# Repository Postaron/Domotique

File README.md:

#Domotique

Projet en cours pour contrôler la température/radiateur et la lumière/luminosité par le biais du RFID 
(tag) et d'un petit écran LCD, le tout par le bus I²C

#Projet non fini

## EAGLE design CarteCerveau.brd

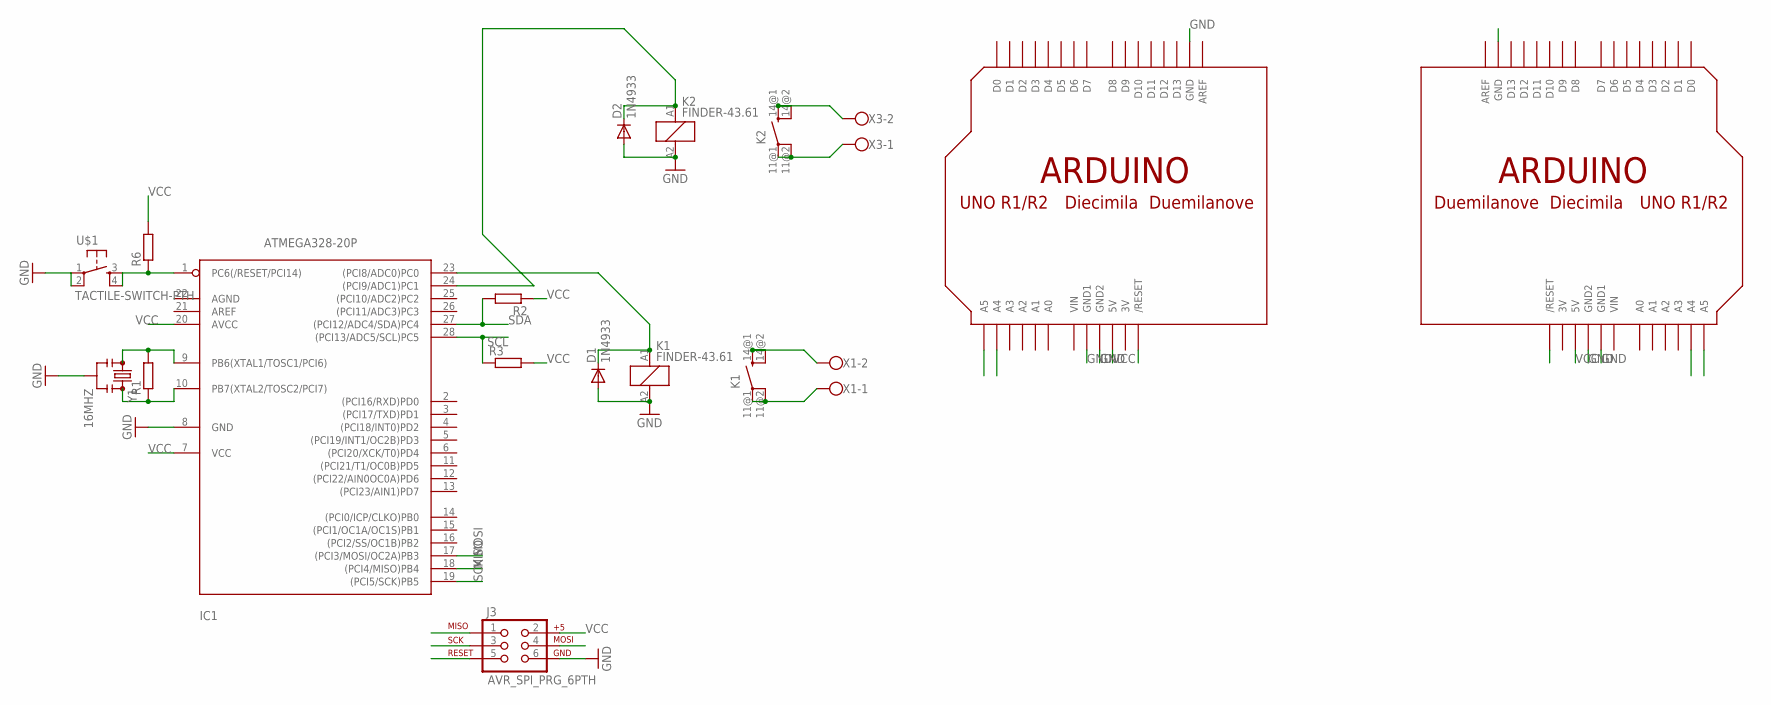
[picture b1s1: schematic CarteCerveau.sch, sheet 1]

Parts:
D1, D2: 1N4933; DO41-10
IC1: ATMEGA328-20P; DIL28-3
J3: AVR_SPI_PRG_6PTH; 2X3
K1, K2: FINDER-43.61
R1, R2, R3, R6: R-EU_R1206; R1206
U$1: TACTILE-SWITCH-PTH; TAC-SWITCH-PTH
U$2, U$3: ARDUINO-NOHOLE
X1, X3: W237-102
Y1: 16MHZ; RESONATOR-SMD

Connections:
3V: U$2.3V, U$3.3V
GND: D1.A, D2.A, IC1.8 (GND), J3.6, K1.A2 (2), K2.A2 (2), U$1.1, U$1.2, U$2.GND, U$2.GND1, U$2.GND2, U$3.GND, U$3.GND1, U$3.GND2, Y1.2; also elsewhere on the board
MISO: IC1.18 ((PCI4/MISO)PB4), J3.1
MOSI: IC1.17 ((PCI3/MOSI/OC2A)PB3), J3.4
unnamed: IC1.9 (PB6(XTAL1/TOSC1/PCI6)), R1.2, Y1.1
unnamed: IC1.10 (PB7(XTAL2/TOSC2/PCI7)), R1.1, Y1.3
unnamed: D1.C, IC1.23 ((PCI8/ADC0)PC0), K1.A1 (1)
unnamed: K1.14@1 (SA), K1.14@2 (SB), X1.2
unnamed: K1.11@1 (PA), K1.11@2 (PB), X1.1
unnamed: D2.C, IC1.24 ((PCI9/ADC1)PC1), K2.A1 (1)
unnamed: K2.14@1 (SA), K2.14@2 (SB), X3.2
unnamed: K2.11@1 (PA), K2.11@2 (PB), X3.1
RST: IC1.1 (PC6(/RESET/PCI14)), J3.5, R6.1, U$1.3, U$1.4, U$2.RESET (/RESET), U$3.RESET (/RESET)
SCK: IC1.19 ((PCI5/SCK)PB5), J3.3
SCL: IC1.28 ((PCI13/ADC5/SCL)PC5), R3.1, U$2.A5, U$3.A5
SDA: IC1.27 ((PCI12/ADC4/SDA)PC4), R2.2, U$2.A4, U$3.A4
VCC: IC1.7 (VCC), IC1.20 (AVCC), J3.2, R2.1, R3.2, R6.2, U$2.5V, U$3.5V; also elsewhere on the board
VIN: U$2.VIN, U$3.VIN

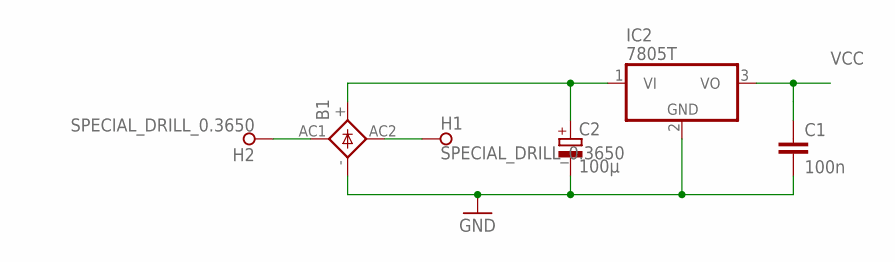
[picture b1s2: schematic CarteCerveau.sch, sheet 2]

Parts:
B1: 2KBB-R
C1: 100n; C1206
C2: 100µ; B45181A
H1, H2: SPECIAL_DRILL_0.3650; PAD_0.3650
IC2: 7805T; TO220H

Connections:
GND: B1.-, C1.2, C2.-, IC2.2 (GND); also elsewhere on the board
unnamed: B1.AC1, H2.1
unnamed: B1.AC2, H1.1
unnamed: B1.+, C2.+, IC2.1 (VI)
VCC: C1.1, IC2.3 (VO); also elsewhere on the board

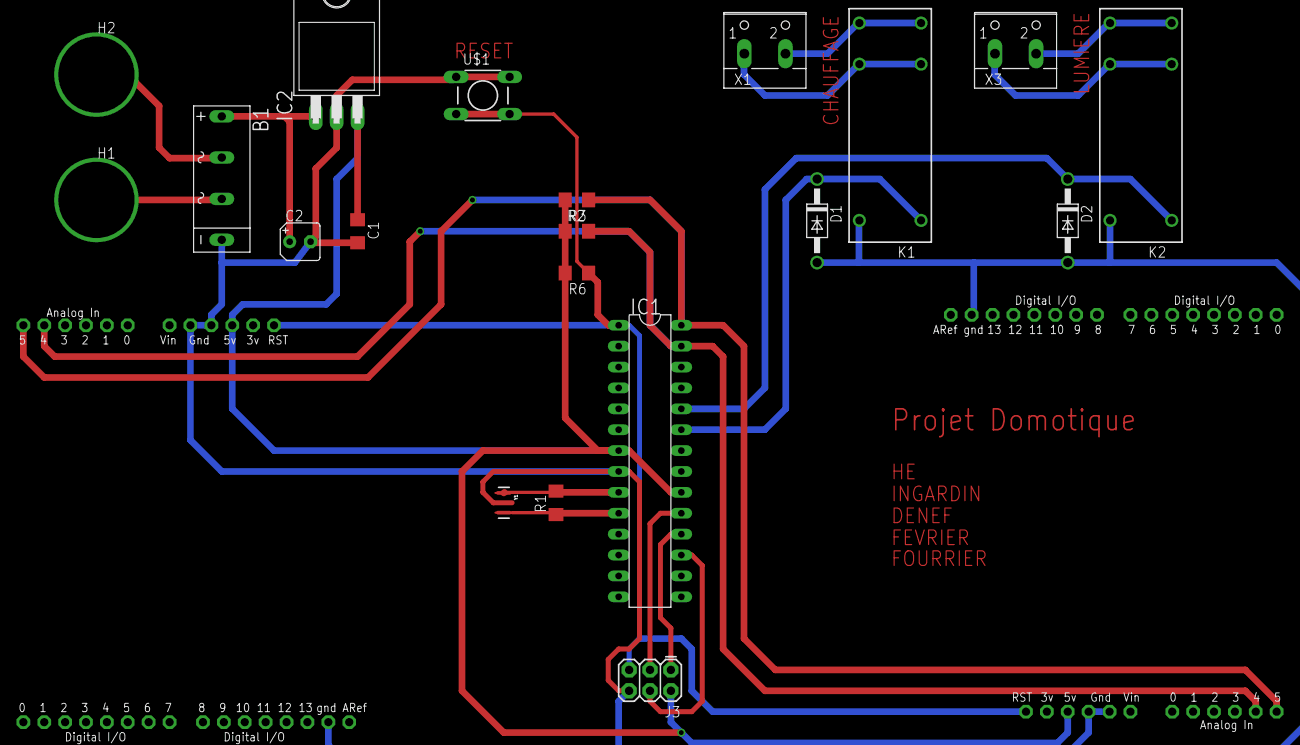
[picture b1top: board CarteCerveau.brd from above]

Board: 2 copper layers, 22 parts (0 on the bottom side), 21 nets.

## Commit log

2016-06-20 add description in README
2016-06-20 added rfid address (#define)
2016-06-20 remove some useless comments
2016-06-20 added comments and explanation
2016-06-21 added schematic and board, done from eagle
2017-01-21 some changes, don't remember them anymore

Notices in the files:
parts and their libraries:
SparkFun-Connectors: Licensing: Creative Commons ShareAlike 4.0 International - https://creativecommons.org/licenses/by-sa/4.0
